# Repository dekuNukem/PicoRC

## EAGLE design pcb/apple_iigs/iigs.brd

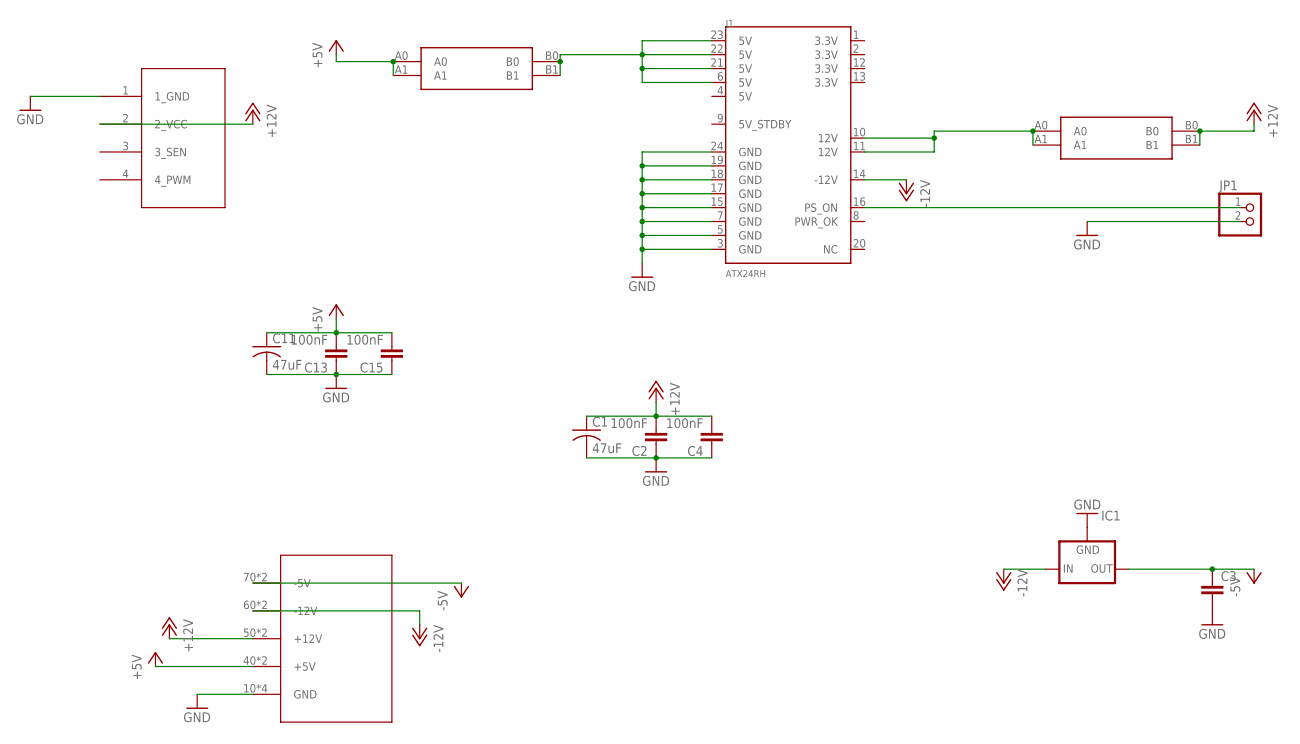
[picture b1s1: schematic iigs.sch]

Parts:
C1, C11: 47uF; C1210
C2, C4, C13, C15: 100nF; 0805@1
C3: C5/2.5; C5B2.5
IC1: 79XXS
J1: ATX24RH; ATX24_RIGHT_ANGLE
JP1: PINHD-1X2; 1X02
JP4: 4PIN_FAN; 1X04
U$1, U$2: CAR_FUSE_HOLDER3IN1; FUSE_HOLDER_3IN1
U$7: 3.96_FEM_IIGS; 3.96_FEMALE_IIGS_GAP

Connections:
+5V: C11.1, C13.2, C15.2, U$1.A0, U$1.A1, U$7.40 (+5V), U$7.41 (+5V)
+12V: C1.1, C2.2, C4.2, JP4.2 (2_VCC), U$2.B0, U$2.B1, U$7.50 (+12V), U$7.51 (+12V)
-5V: C3.1, IC1.OUT, U$7.70 (-5V), U$7.71 (-5V)
-12V: IC1.IN, J1.14 (-12V), U$7.60 (-12V), U$7.61 (-12V)
GND: C1.2, C2.1, C3.2, C4.1, C11.2, C13.1, C15.1, IC1.GND, J1.3 (GND), J1.5 (GND), J1.7 (GND), J1.15 (GND), J1.17 (GND), J1.18 (GND), J1.19 (GND), J1.24 (GND), JP1.2, JP4.1 (1_GND), U$7.10 (GND), U$7.11 (GND), U$7.20 (GND), U$7.21 (GND)
unnamed: J1.16 (PS_ON), JP1.1
unnamed: J1.6 (5V), J1.21 (5V), J1.22 (5V), J1.23 (5V), U$1.B0, U$1.B1
unnamed: J1.10 (12V), J1.11 (12V), U$2.A0, U$2.A1

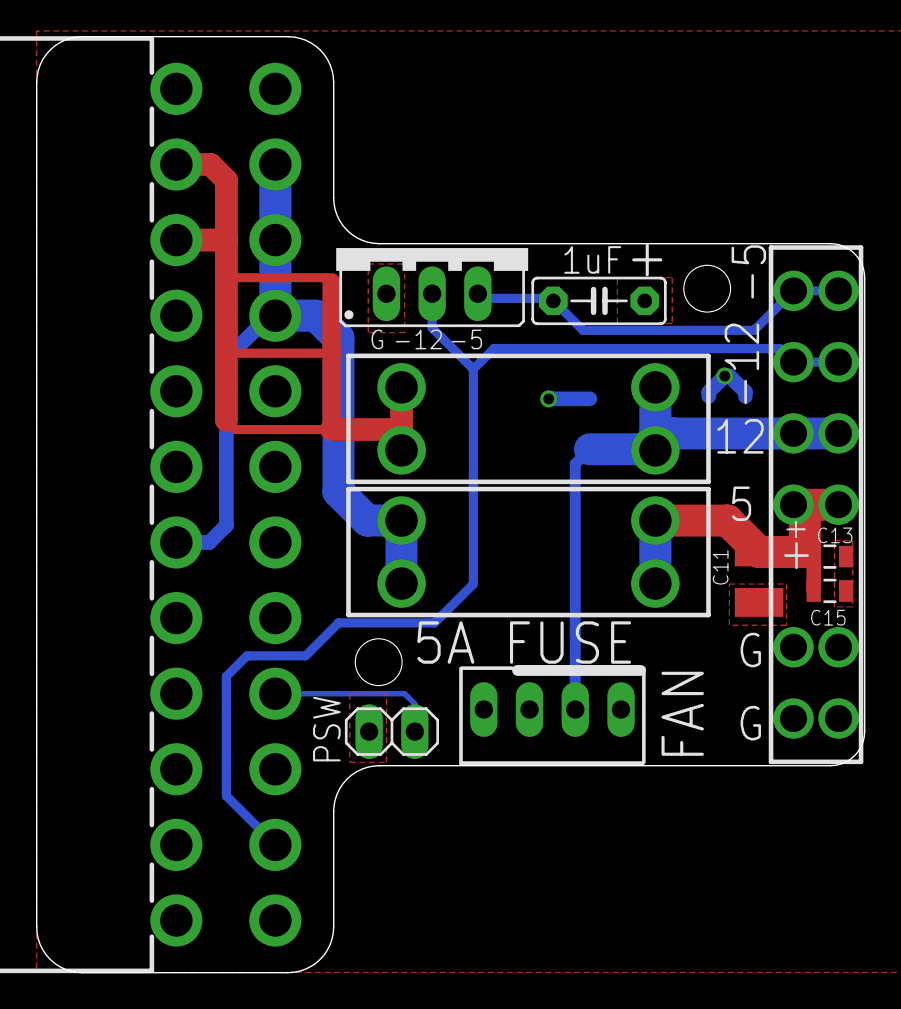
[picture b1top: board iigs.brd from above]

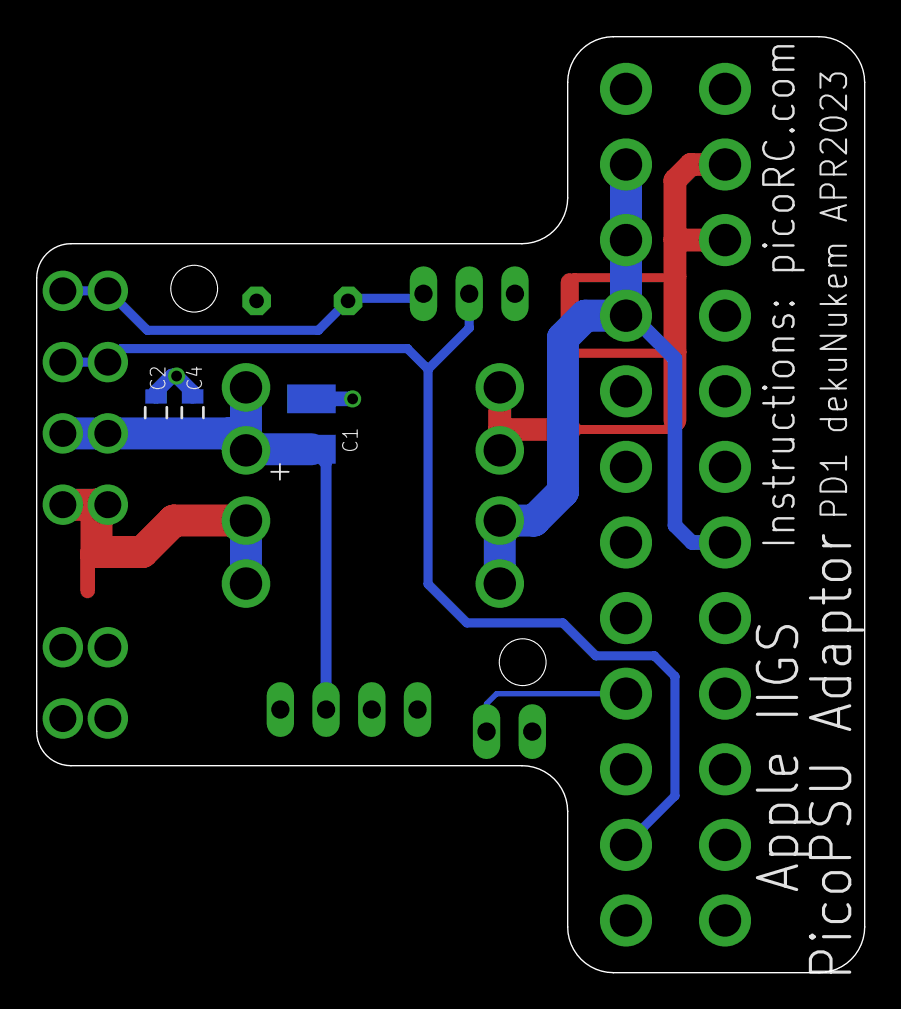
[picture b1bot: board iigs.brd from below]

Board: 2 copper layers, 46.0 x 52.0 mm, 14 parts (3 on the bottom side), 8 nets.

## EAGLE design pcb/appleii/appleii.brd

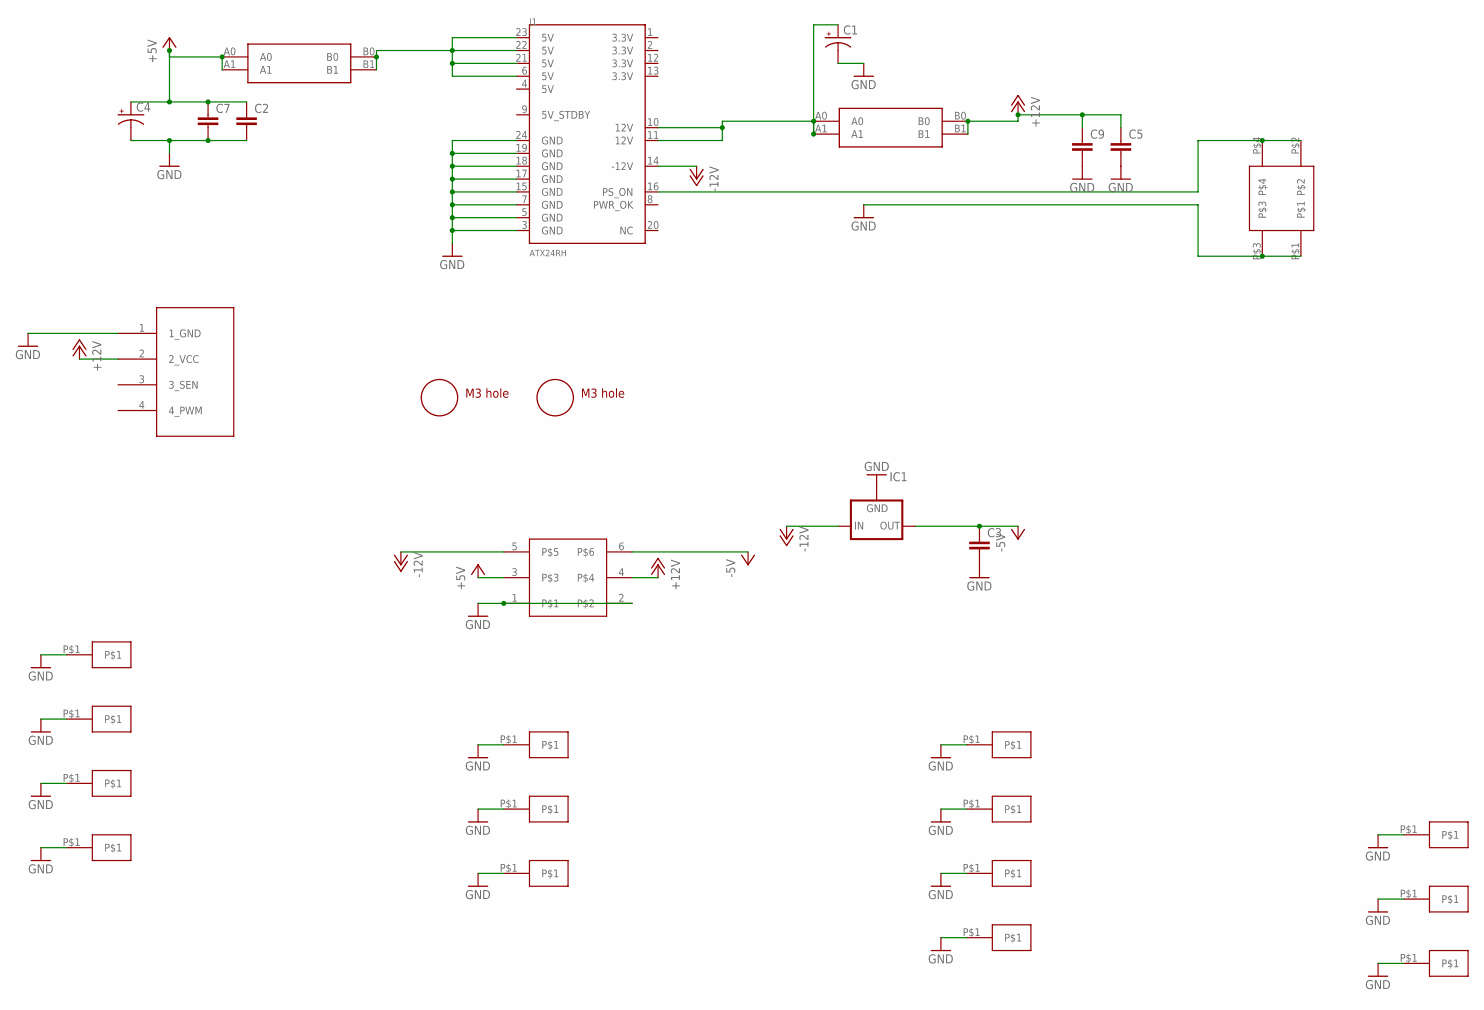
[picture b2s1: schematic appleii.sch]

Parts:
C1, C4: CPOL-USE3.5-8; E3,5-8
C2, C3, C5, C7, C9: C5/2.5; C5B2.5
IC1: 79XXS
J1: ATX24RH; ATX24_RIGHT_ANGLE
JP3: 4PIN_FAN; 1X04
U$1, U$2: CAR_FUSE_HOLDER3IN1; FUSE_HOLDER_3IN1
U$3: ROCK_SW; ROCK_SWITCH
U$4, U$5: M3_MOUNTING_HOLE; M3_MOUNTING_HOLE_PACK
U$6: APPLEII
U$7, U$8, U$9, U$10, U$11, U$12, U$13, U$14, U$15, U$16, U$17, U$18, U$19, U$20: EDGEPAD

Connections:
+5V: C2.1, C4.+, C7.1, U$1.A0, U$1.A1, U$6.3
+12V: C5.1, C9.1, JP3.2 (2_VCC), U$2.B0, U$2.B1, U$6.4
-5V: C3.1, IC1.OUT, U$6.6
-12V: IC1.IN, J1.14 (-12V), U$6.5
GND: C1.-, C2.2, C3.2, C4.-, C5.2, C7.2, C9.2, IC1.GND, J1.3 (GND), J1.5 (GND), J1.7 (GND), J1.15 (GND), J1.17 (GND), J1.18 (GND), J1.19 (GND), J1.24 (GND), JP3.1 (1_GND), U$3.P$1, U$3.P$3, U$6.1, U$6.2, U$7.P$1, U$8.P$1, U$9.P$1, U$10.P$1, U$11.P$1, U$12.P$1, U$13.P$1, U$14.P$1, U$15.P$1, U$16.P$1, U$17.P$1, U$18.P$1, U$19.P$1, U$20.P$1
unnamed: J1.16 (PS_ON), U$3.P$2, U$3.P$4
unnamed: J1.6 (5V), J1.21 (5V), J1.22 (5V), J1.23 (5V), U$1.B0, U$1.B1
unnamed: C1.+, J1.10 (12V), J1.11 (12V), U$2.A0, U$2.A1

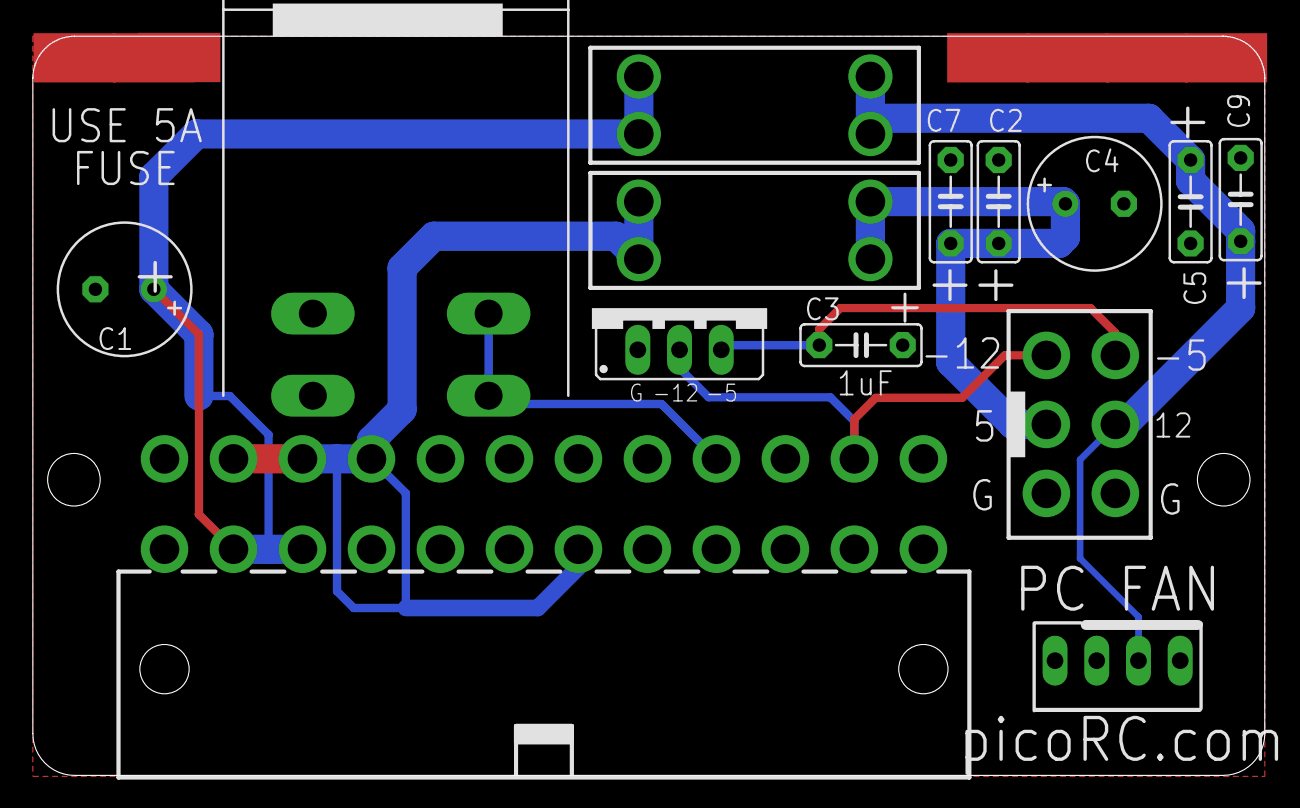
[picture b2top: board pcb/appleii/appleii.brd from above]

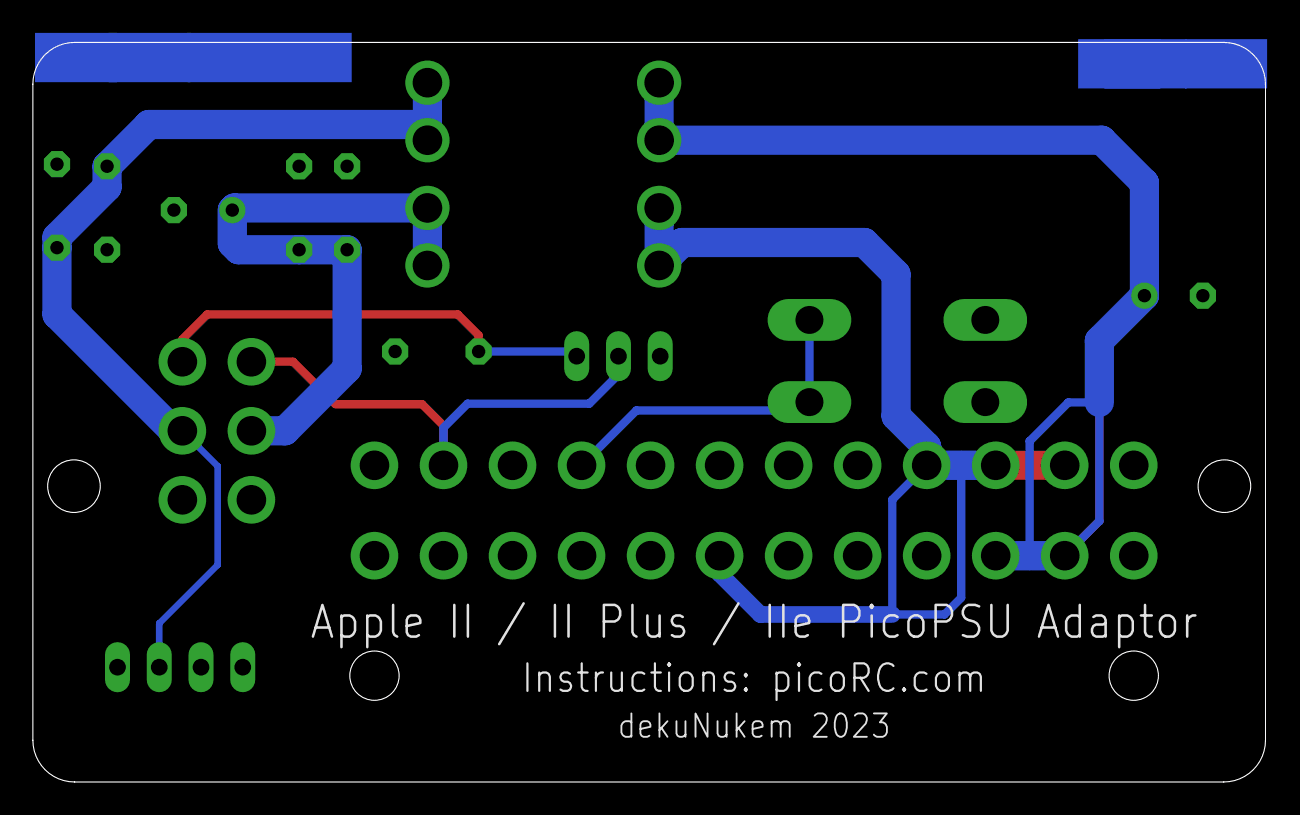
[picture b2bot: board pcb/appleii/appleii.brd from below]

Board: 2 copper layers, 75.0 x 45.0 mm, 30 parts (7 on the bottom side), 8 nets.

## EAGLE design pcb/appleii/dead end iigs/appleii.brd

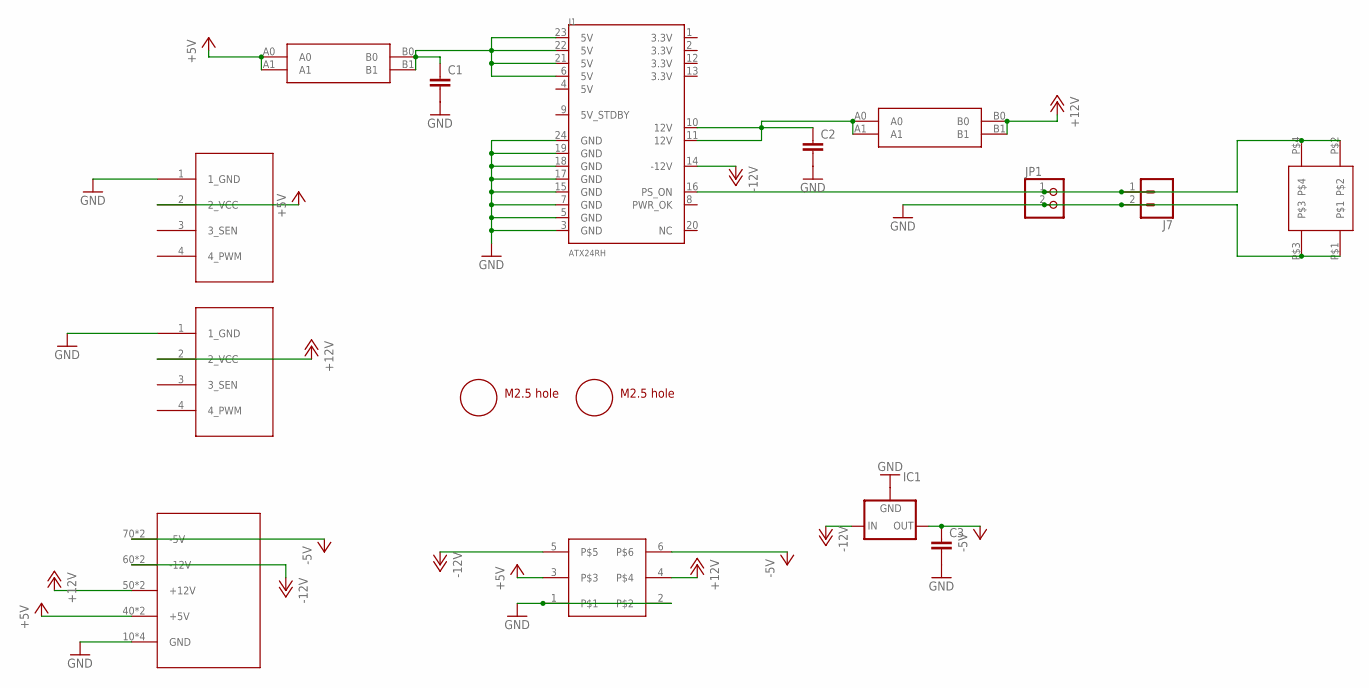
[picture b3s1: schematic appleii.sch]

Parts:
C1, C2, C3: C5/2.5; C5B2.5
IC1: 79XXS
J1: ATX24RH; ATX24_RIGHT_ANGLE
J7: CONN_023.5MM-NO_SILK; SCREWTERMINAL-3.5MM-2-NS
JP1: PINHD-1X2; 1X02
JP3, JP4: 4PIN_FAN; 1X04
U$1, U$2: CAR_FUSE_HOLDER3IN1; FUSE_HOLDER_3IN1
U$3: ROCK_SW; ROCK_SWITCH
U$4, U$5: M2.5_MOUNTING_HOLE; M3_MOUNTING_HOLE_PACK
U$6: APPLEII
U$7: 3.96_FEM_IIGS; 3.96_FEMALE_IIGS_GAP

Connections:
+5V: JP4.2 (2_VCC), U$1.A0, U$1.A1, U$6.3, U$7.40 (+5V), U$7.41 (+5V)
+12V: JP3.2 (2_VCC), U$2.B0, U$2.B1, U$6.4, U$7.50 (+12V), U$7.51 (+12V)
-5V: C3.1, IC1.OUT, U$6.6, U$7.70 (-5V), U$7.71 (-5V)
-12V: IC1.IN, J1.14 (-12V), U$6.5, U$7.60 (-12V), U$7.61 (-12V)
GND: C1.2, C2.2, C3.2, IC1.GND, J1.3 (GND), J1.5 (GND), J1.7 (GND), J1.15 (GND), J1.17 (GND), J1.18 (GND), J1.19 (GND), J1.24 (GND), J7.2, JP1.2, JP3.1 (1_GND), JP4.1 (1_GND), U$3.P$1, U$3.P$3, U$6.1, U$6.2, U$7.10 (GND), U$7.11 (GND), U$7.20 (GND), U$7.21 (GND)
unnamed: J1.16 (PS_ON), J7.1, JP1.1, U$3.P$2, U$3.P$4
unnamed: C1.1, J1.6 (5V), J1.21 (5V), J1.22 (5V), J1.23 (5V), U$1.B0, U$1.B1
unnamed: C2.1, J1.10 (12V), J1.11 (12V), U$2.A0, U$2.A1

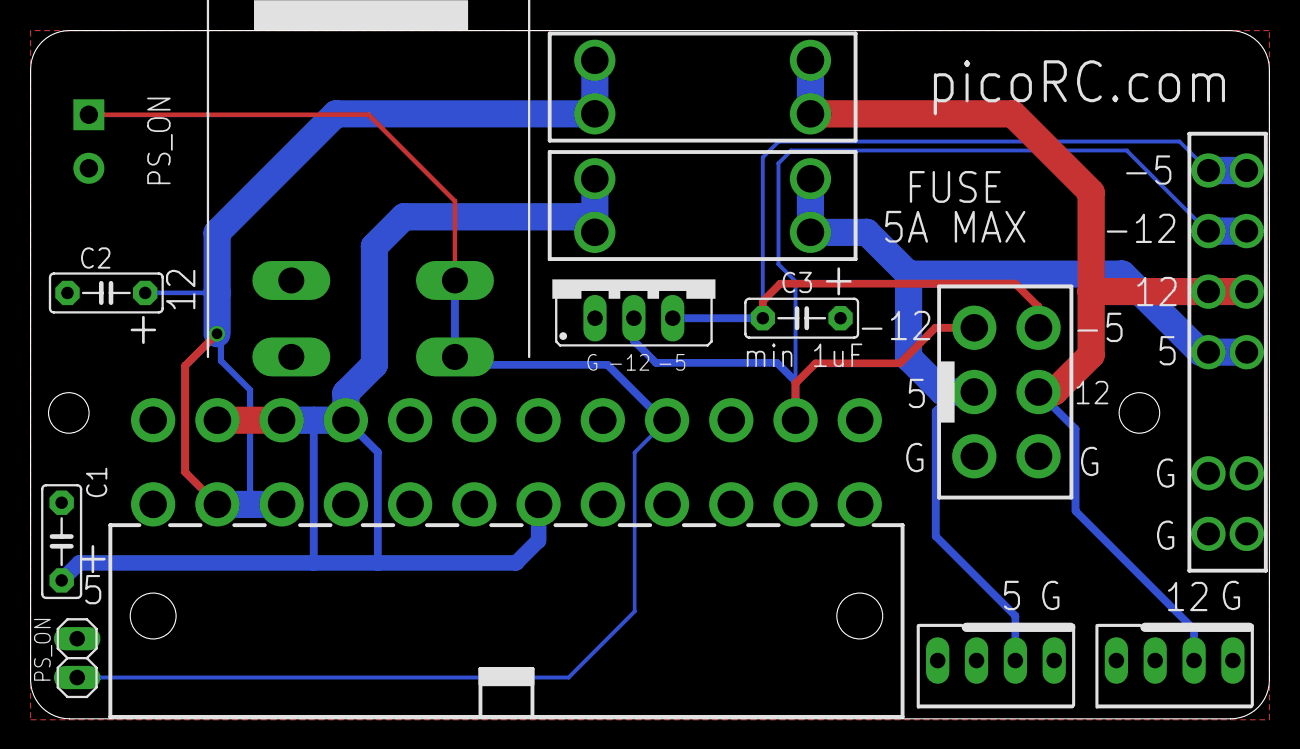
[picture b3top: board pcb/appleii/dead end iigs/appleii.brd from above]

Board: 2 copper layers, 81.0 x 45.0 mm, 16 parts (0 on the bottom side), 8 nets.

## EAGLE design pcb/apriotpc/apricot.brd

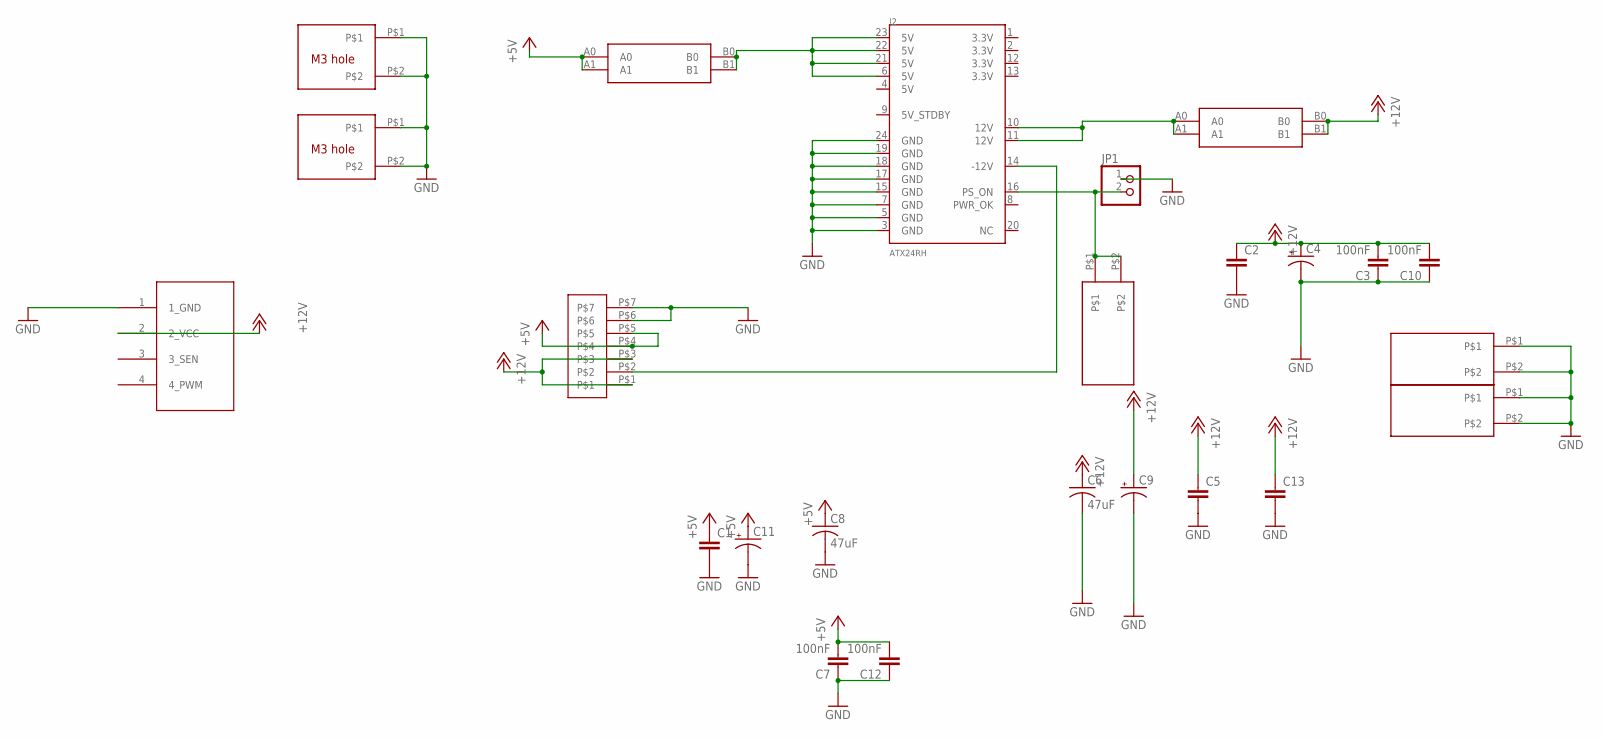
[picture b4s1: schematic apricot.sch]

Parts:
C1, C2, C5, C13: C5/2.5; C5B2.5
C3, C7, C10, C12: 100nF; 0805@1
C4, C9, C11: CPOL-USE3.5-8; E3,5-8
C6, C8: 47uF; C1210
J2: ATX24RH; ATX24_RIGHT_ANGLE
JP1: PINHD-1X2; 1X02
JP3: 4PIN_FAN; 1X04
U$1, U$3, U$7: 6MM_BLADE; 6.2MMBLADE
U$2, U$8: CAR_FUSE_HOLDER3IN1; FUSE_HOLDER_3IN1
U$4: VH396; 396_7P
U$5, U$6: M3_MOUNTING_HOLE; M3_MOUNTING_HOLE_PACK

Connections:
+5V: C1.1, C7.2, C8.1, C11.+, C12.2, U$4.P$4, U$4.P$5, U$8.A0, U$8.A1
+12V: C2.1, C3.2, C4.+, C5.1, C6.1, C9.+, C10.2, C13.1, JP3.2 (2_VCC), U$2.B0, U$2.B1, U$4.P$1, U$4.P$3
GND: C1.2, C2.2, C3.1, C4.-, C5.2, C6.2, C7.1, C8.2, C9.-, C10.1, C11.-, C12.1, C13.2, J2.3 (GND), J2.5 (GND), J2.7 (GND), J2.15 (GND), J2.17 (GND), J2.18 (GND), J2.19 (GND), J2.24 (GND), JP1.1, JP3.1 (1_GND), U$3.P$1, U$3.P$2, U$4.P$6, U$4.P$7, U$5.P$1, U$5.P$2, U$6.P$1, U$6.P$2, U$7.P$1, U$7.P$2
unnamed: J2.16 (PS_ON), JP1.2, U$1.P$1, U$1.P$2
unnamed: J2.14 (-12V), U$4.P$2
unnamed: J2.6 (5V), J2.21 (5V), J2.22 (5V), J2.23 (5V), U$8.B0, U$8.B1
unnamed: J2.10 (12V), J2.11 (12V), U$2.A0, U$2.A1

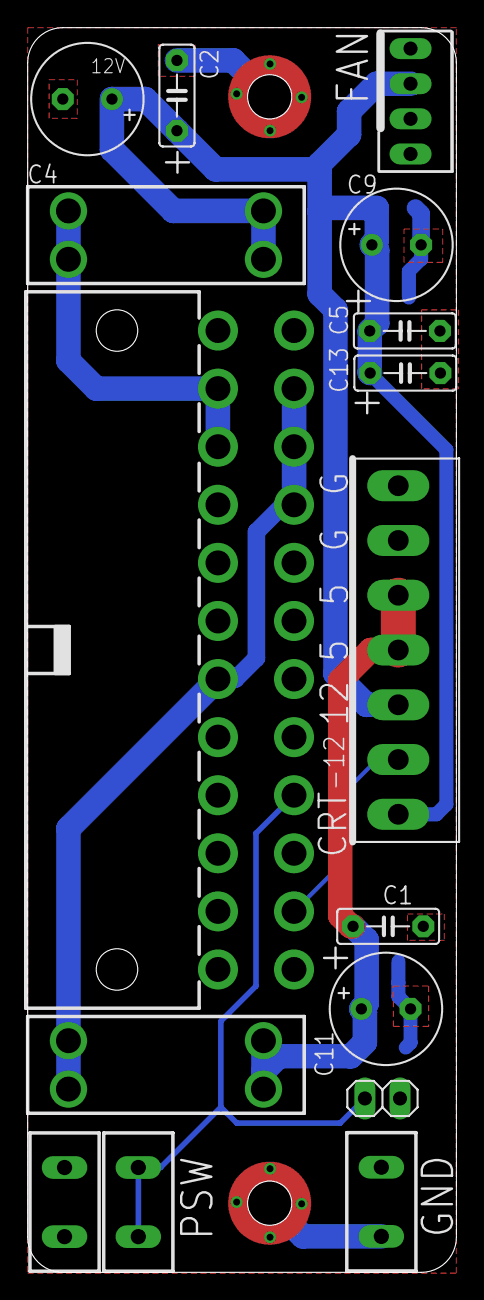
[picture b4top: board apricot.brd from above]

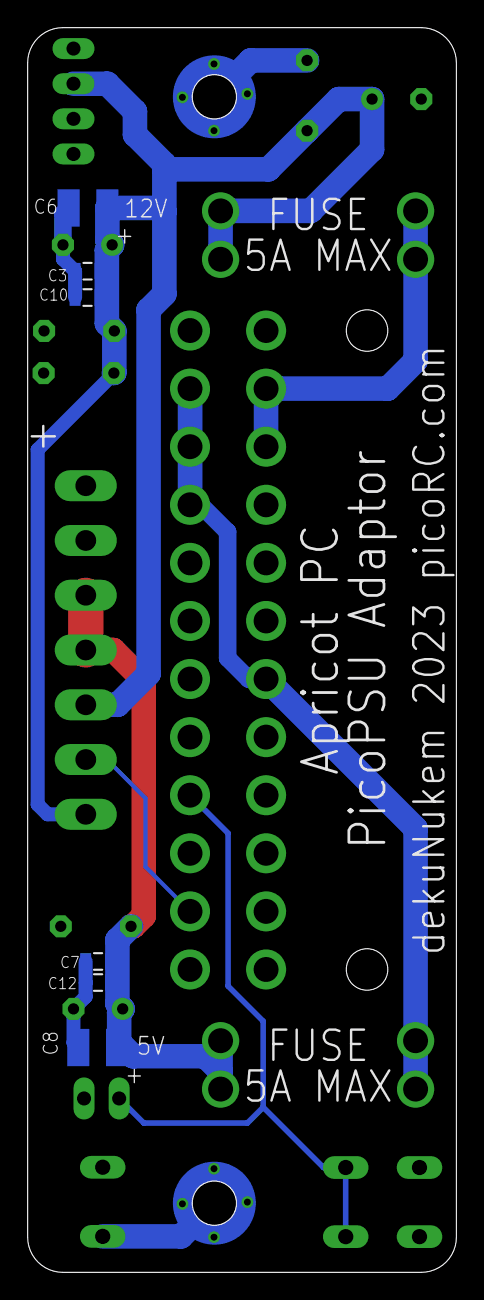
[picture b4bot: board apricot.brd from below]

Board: 2 copper layers, 31.0 x 90.0 mm, 24 parts (6 on the bottom side), 7 nets.

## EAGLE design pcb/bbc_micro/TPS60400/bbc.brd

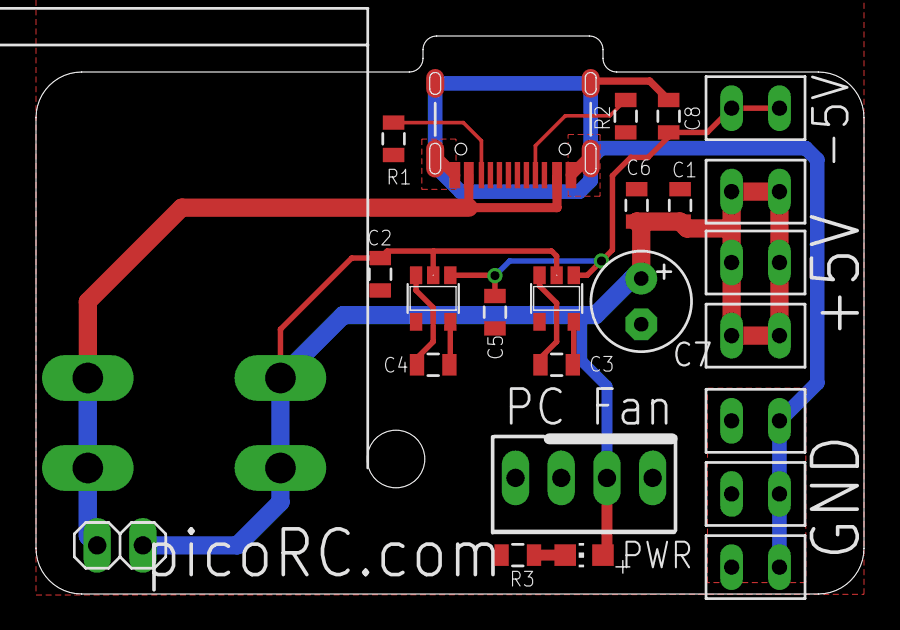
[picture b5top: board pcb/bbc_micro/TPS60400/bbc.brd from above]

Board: 2 copper layers, 46.0 x 31.0 mm, 26 parts (0 on the bottom side), 11 nets.

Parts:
C1, C8: 100nF; 0805@1
C2, C3, C4, C6: 1uF; 0805@1
C5: 2.2uF; 0805@1
C7: E2,5-6
J4: USB-C-16P
JP1: 1X02
JP3: 1X04
LED3: CHIP-LED0805
R1, R2, R3: 5K1; 0805
U1, U3: TPS60400DVBR; SOT23-5
U$3: ROCK_SW; ROCK_SWITCH
U$4: M3_MOUNTING_HOLE; M3_MOUNTING_HOLE_PACK
U$5, U$6, U$7, U$8, U$9, U$10, U$11: BLADE28; 2.8BLADE

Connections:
+5V: C1.2, C2.2, C6.2, C7.+, JP1.1, JP3.2, LED3.A, U1.2, U3.2, U$3.P$2, U$3.P$4, U$6.P$1, U$6.P$2, U$7.P$1, U$7.P$2, U$8.P$1, U$8.P$2
-5V: C5.1, C8.2, U1.1, U3.1, U$5.P$1, U$5.P$2
GND: C1.1, C2.1, C5.2, C6.1, C7.-, C8.1, J4.GND, J4.GND2, J4.SHLD1, J4.SHLD2, J4.SHLD3, J4.SHLD4, J4.SHLD5, J4.SHLD6, J4.SHLD7, J4.SHLD8, JP3.1, R1.2, R2.2, R3.1, U1.4, U3.4, U$9.P$1, U$9.P$2, U$10.P$1, U$10.P$2, U$11.P$1, U$11.P$2
unnamed: J4.VBUS1, J4.VBUS2, JP1.2, U$3.P$1, U$3.P$3
unnamed: C3.2, U3.3
unnamed: C3.1, U3.5
unnamed: C4.2, U1.3
unnamed: C4.1, U1.5
unnamed: J4.A5, R2.1
unnamed: LED3.C, R3.2
unnamed: J4.B5, R1.1

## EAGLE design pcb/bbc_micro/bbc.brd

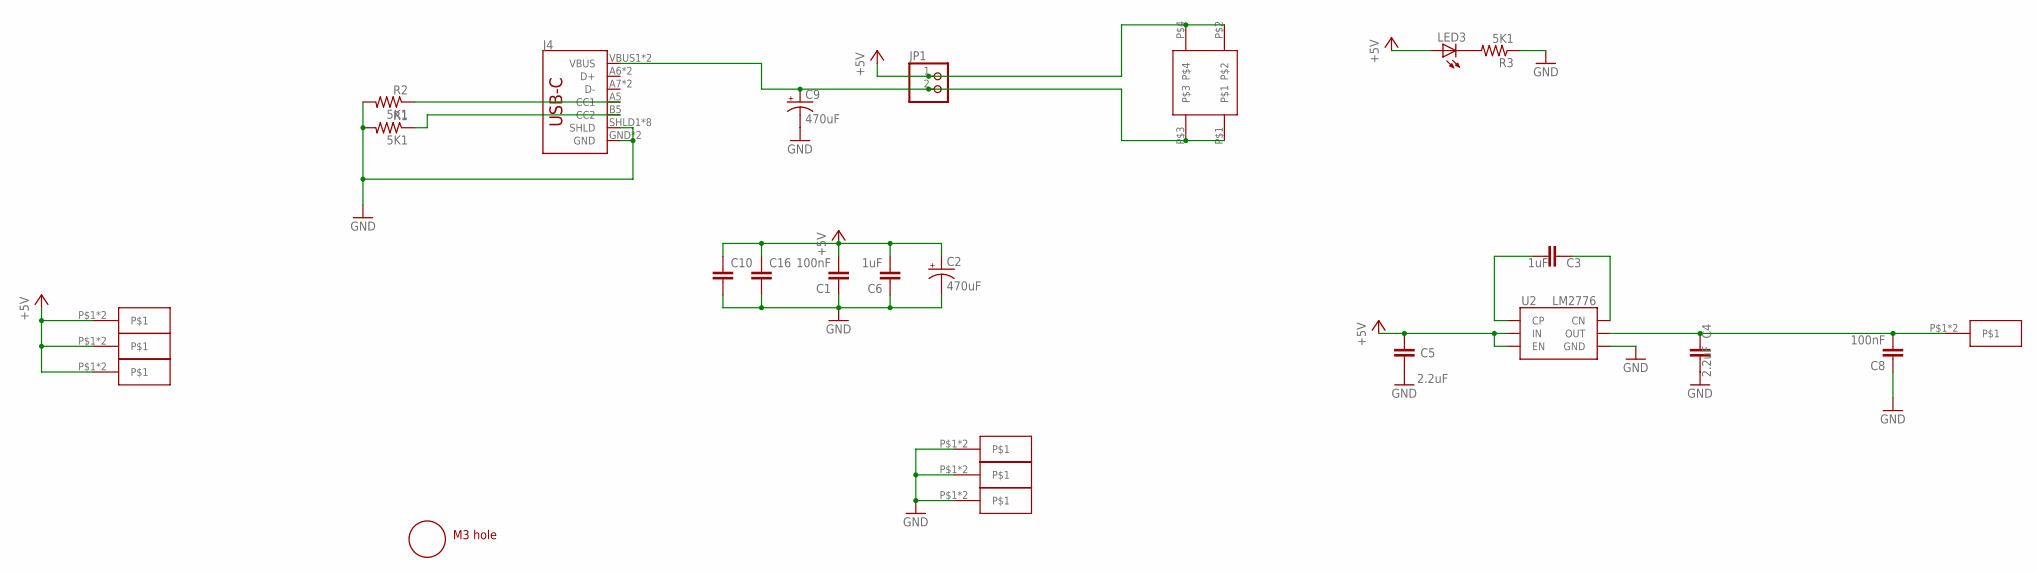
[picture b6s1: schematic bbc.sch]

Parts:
C1, C8: 100nF; 0805@1
C2, C9: 470uF; SMC_D
C3, C6: 1uF; 0805@1
C4, C5: 2.2uF; 0805@1
C10, C16: C5/2.5; C5B2.5
J4: USB_C16PIN; USB-C-16P
JP1: PINHD-1X2; 1X02
LED3: LEDCHIP-LED0805; CHIP-LED0805
R1, R2, R3: 5K1; 0805
U2: LM2776; SOT-23-6
U$3: ROCK_SW; ROCK_SWITCH
U$4: M3_MOUNTING_HOLE; M3_MOUNTING_HOLE_PACK
U$5, U$6, U$7, U$8, U$9, U$10, U$11: BLADE28; 2.8BLADE

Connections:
+5V: C1.2, C2.+, C5.1, C6.2, C10.1, C16.1, JP1.1, LED3.A, U2.3 (IN), U2.4 (EN), U$3.P$2, U$3.P$4, U$6.P$1, U$6.P$2, U$7.P$1, U$7.P$2, U$8.P$1, U$8.P$2
GND: C1.1, C2.-, C4.2, C5.2, C6.1, C8.1, C9.-, C10.2, C16.2, J4.GND, J4.GND2 (GND), J4.SHLD1 (SHLD), J4.SHLD2 (SHLD), J4.SHLD3 (SHLD), J4.SHLD4 (SHLD), J4.SHLD5 (SHLD), J4.SHLD6 (SHLD), J4.SHLD7 (SHLD), J4.SHLD8 (SHLD), R1.2, R2.2, R3.1, U2.2 (GND), U$9.P$1, U$9.P$2, U$10.P$1, U$10.P$2, U$11.P$1, U$11.P$2
unnamed: C9.+, J4.VBUS1 (VBUS), J4.VBUS2 (VBUS), JP1.2, U$3.P$1, U$3.P$3
unnamed: C3.2, U2.5 (CP)
unnamed: C3.1, U2.6 (CN)
unnamed: C4.1, C8.2, U2.1 (OUT), U$5.P$1, U$5.P$2
unnamed: J4.A5 (CC1), R2.1
unnamed: LED3.C, R3.2
unnamed: J4.B5 (CC2), R1.1

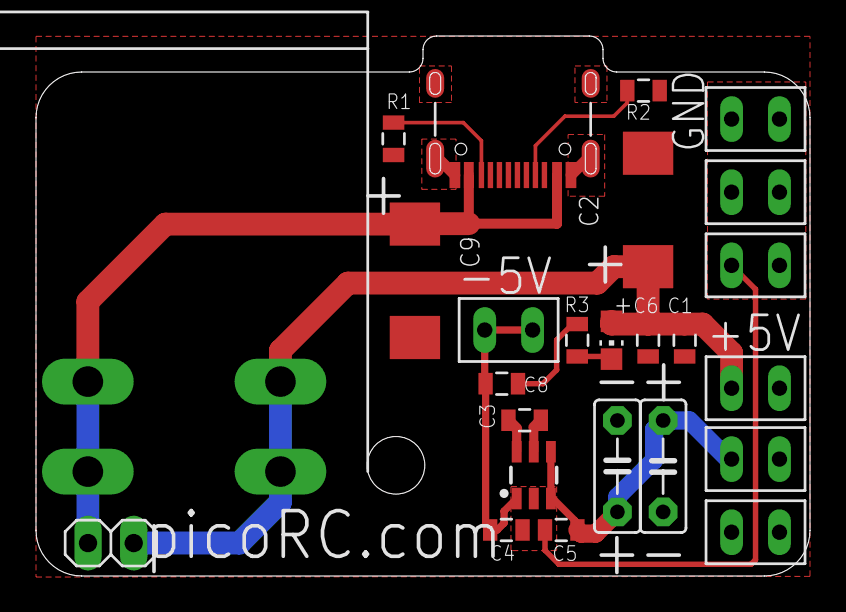
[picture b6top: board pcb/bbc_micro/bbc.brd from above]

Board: 2 copper layers, 43.0 x 30.0 mm, 26 parts (0 on the bottom side), 9 nets.

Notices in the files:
parts and their libraries:
SparkFun-Connectors: Licensing: Creative Commons ShareAlike 4.0 International - https://creativecommons.org/licenses/by-sa/4.0
